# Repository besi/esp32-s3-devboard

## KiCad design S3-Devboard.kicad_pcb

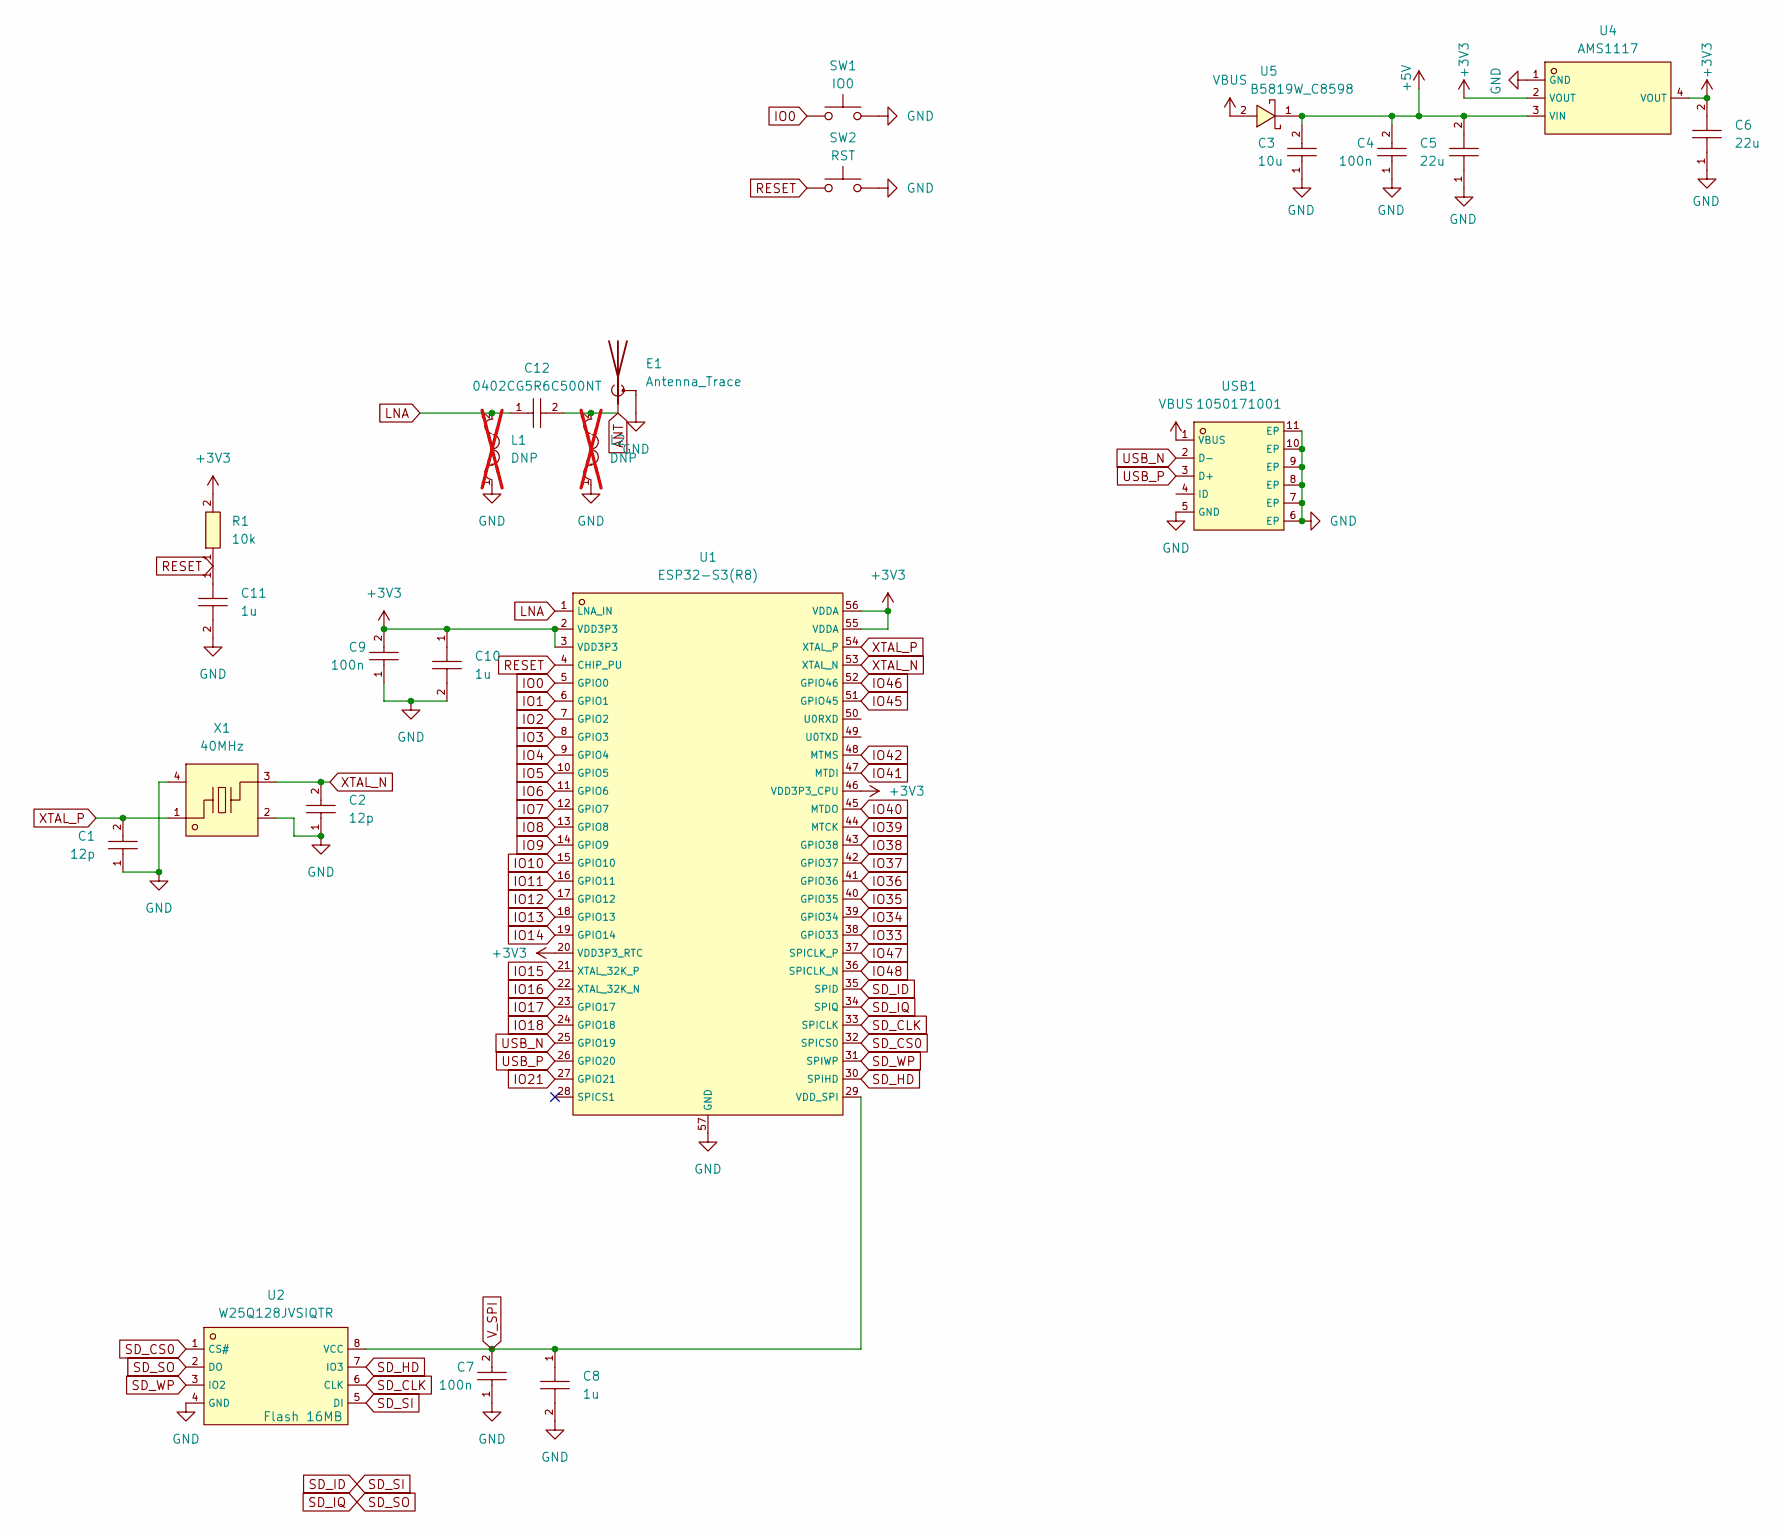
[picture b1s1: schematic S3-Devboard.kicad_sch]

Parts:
C1, C2: 12p; C0402; LCSC C1547
C3: 10u; C0402; LCSC C15525
C4, C7, C9: 100n; C0402; LCSC C1525
C5, C6: 22u; C0603; LCSC C59461
C8, C10, C11: 1u; C0402; LCSC C52923
C12: 0402CG5R6C500NT; C0402; LCSC C1574
E1: Antenna_Trace; Texas_SWRA117D_2.4GHz_Right
L1, L2: DNP; L0603; LCSC C1035; not fitted
R1: 10k; R0402; LCSC C25744
SW1: IO0; SW_Push_1P1T_NO_Vertical_Wuerth_434133025816
SW2: RST; SW_Push_1P1T_NO_Vertical_Wuerth_434133025816
U1: ESP32-S3(R8); QFN-56_L7.0-W7.0-P0.40-TL-EP4.0; LCSC C2913194
U2: W25Q128JVSIQTR; SOIC-8_L5.3-W5.3-P1.27-LS8.0-BL; LCSC C97521
U4: AMS1117; SOT-223-3_L6.5-W3.4-P2.30-LS7.0-BR; LCSC C6186
U5: B5819W_C8598; SOD-123_L2.7-W1.6-LS3.7-RD-1; LCSC C8598
USB1: 1050171001; MICRO-USB-SMD_1050171001; LCSC C505111
X1: 40MHz; CRYSTAL-SMD_4P-L3.2-W2.5-BL; LCSC C5186937

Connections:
+3V3: C6.2, C9.2, C10.1, R1.2, U1.2 (VDD3P3), U1.3 (VDD3P3), U1.20 (VDD3P3_RTC), U1.46 (VDD3P3_CPU), U1.55 (VDDA), U1.56 (VDDA), U4.2 (VOUT), U4.4 (VOUT)
+5V: C3.2, C4.2, C5.2, U4.3 (VIN), U5.1 (-)
ANT: C12.2, E1.1 (A), L2.2
GND: C1.1, C2.1, C3.1, C4.1, C5.1, C6.1, C7.1, C8.2, C9.1, C10.2, C11.2, E1.2 (Shield), L1.1, L2.1, SW1.1, SW2.1, U1.57 (GND), U2.4 (GND), U4.1 (GND), USB1.5 (GND), USB1.6 (EP), USB1.7 (EP), USB1.8 (EP), USB1.9 (EP), USB1.10 (EP), USB1.11 (EP), X1.2 (GND), X1.4 (GND)
IO0: SW1.2, U1.5 (GPIO0)
IO1: U1.6 (GPIO1)
IO2: U1.7 (GPIO2)
IO3: U1.8 (GPIO3)
IO4: U1.9 (GPIO4)
IO5: U1.10 (GPIO5)
IO6: U1.11 (GPIO6)
IO7: U1.12 (GPIO7)
IO8: U1.13 (GPIO8)
IO9: U1.14 (GPIO9)
IO10: U1.15 (GPIO10)
IO11: U1.16 (GPIO11)
IO12: U1.17 (GPIO12)
IO13: U1.18 (GPIO13)
IO14: U1.19 (GPIO14)
IO15: U1.21 (XTAL_32K_P)
IO16: U1.22 (XTAL_32K_N)
IO17: U1.23 (GPIO17)
IO18: U1.24 (GPIO18)
IO21: U1.27 (GPIO21)
IO33: U1.38 (GPIO33)
IO34: U1.39 (GPIO34)
IO35: U1.40 (GPIO35)
IO36: U1.41 (GPIO36)
IO37: U1.42 (GPIO37)
IO38: U1.43 (GPIO38)
IO39: U1.44 (MTCK)
IO40: U1.45 (MTDO)
IO41: U1.47 (MTDI)
IO42: U1.48 (MTMS)
IO45: U1.51 (GPIO45)
IO46: U1.52 (GPIO46)
IO47: U1.37 (SPICLK_P)
IO48: U1.36 (SPICLK_N)
LNA: C12.1, L1.2, U1.1 (LNA_IN)
RESET: C11.1, R1.1, SW2.2, U1.4 (CHIP_PU)
SD_CLK: U1.33 (SPICLK), U2.6 (CLK)
SD_CS0: U1.32 (SPICS0), U2.1 (CS#)
SD_HD: U1.30 (SPIHD), U2.7 (IO3)
SD_ID: U1.35 (SPID), U2.5 (DI)
SD_IQ: U1.34 (SPIQ), U2.2 (DO)
SD_WP: U1.31 (SPIWP), U2.3 (IO2)
USB_N: U1.25 (GPIO19), USB1.2 (D-)
USB_P: U1.26 (GPIO20), USB1.3 (D+)
VBUS: U5.2 (+), USB1.1 (VBUS)
V_SPI: C7.2, C8.1, U1.29 (VDD_SPI), U2.8 (VCC)
XTAL_N: C2.2, U1.53 (XTAL_N), X1.3
XTAL_P: C1.2, U1.54 (XTAL_P), X1.1

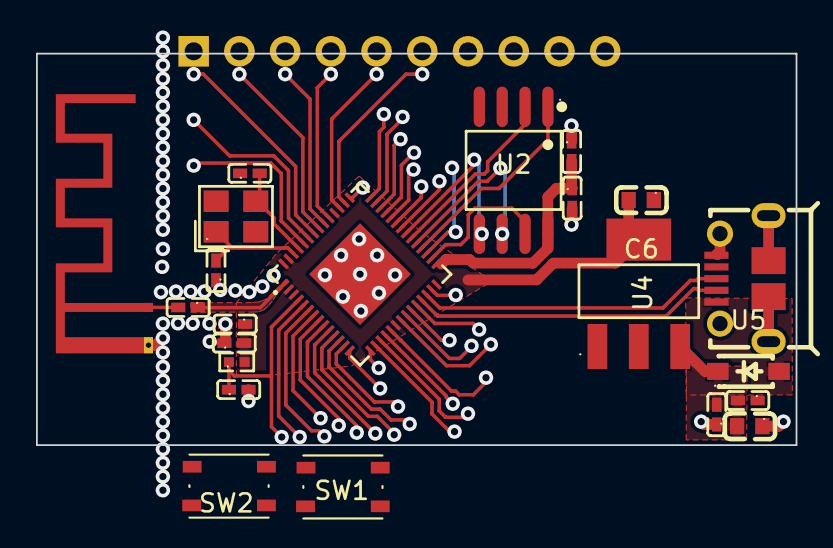
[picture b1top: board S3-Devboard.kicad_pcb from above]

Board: 2 copper layers, 42.2 x 21.8 mm, 22 parts (0 on the bottom side), 19 nets.

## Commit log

2024-07-08 Add empty project
2024-07-08 Add various components
    ESP-S3, 40Mhz crystal, Capacitors, Flash, USB conector etc.
2024-12-28 Updated pins
2025-01-08 Changes
    - Add caps for SPI Flash
    - Add reset circuit
    - Add net classes
    - Add VSPI rather than constant 3V3
    - Add Schottky diode for the power delivery
    - Add PCB Antenna
